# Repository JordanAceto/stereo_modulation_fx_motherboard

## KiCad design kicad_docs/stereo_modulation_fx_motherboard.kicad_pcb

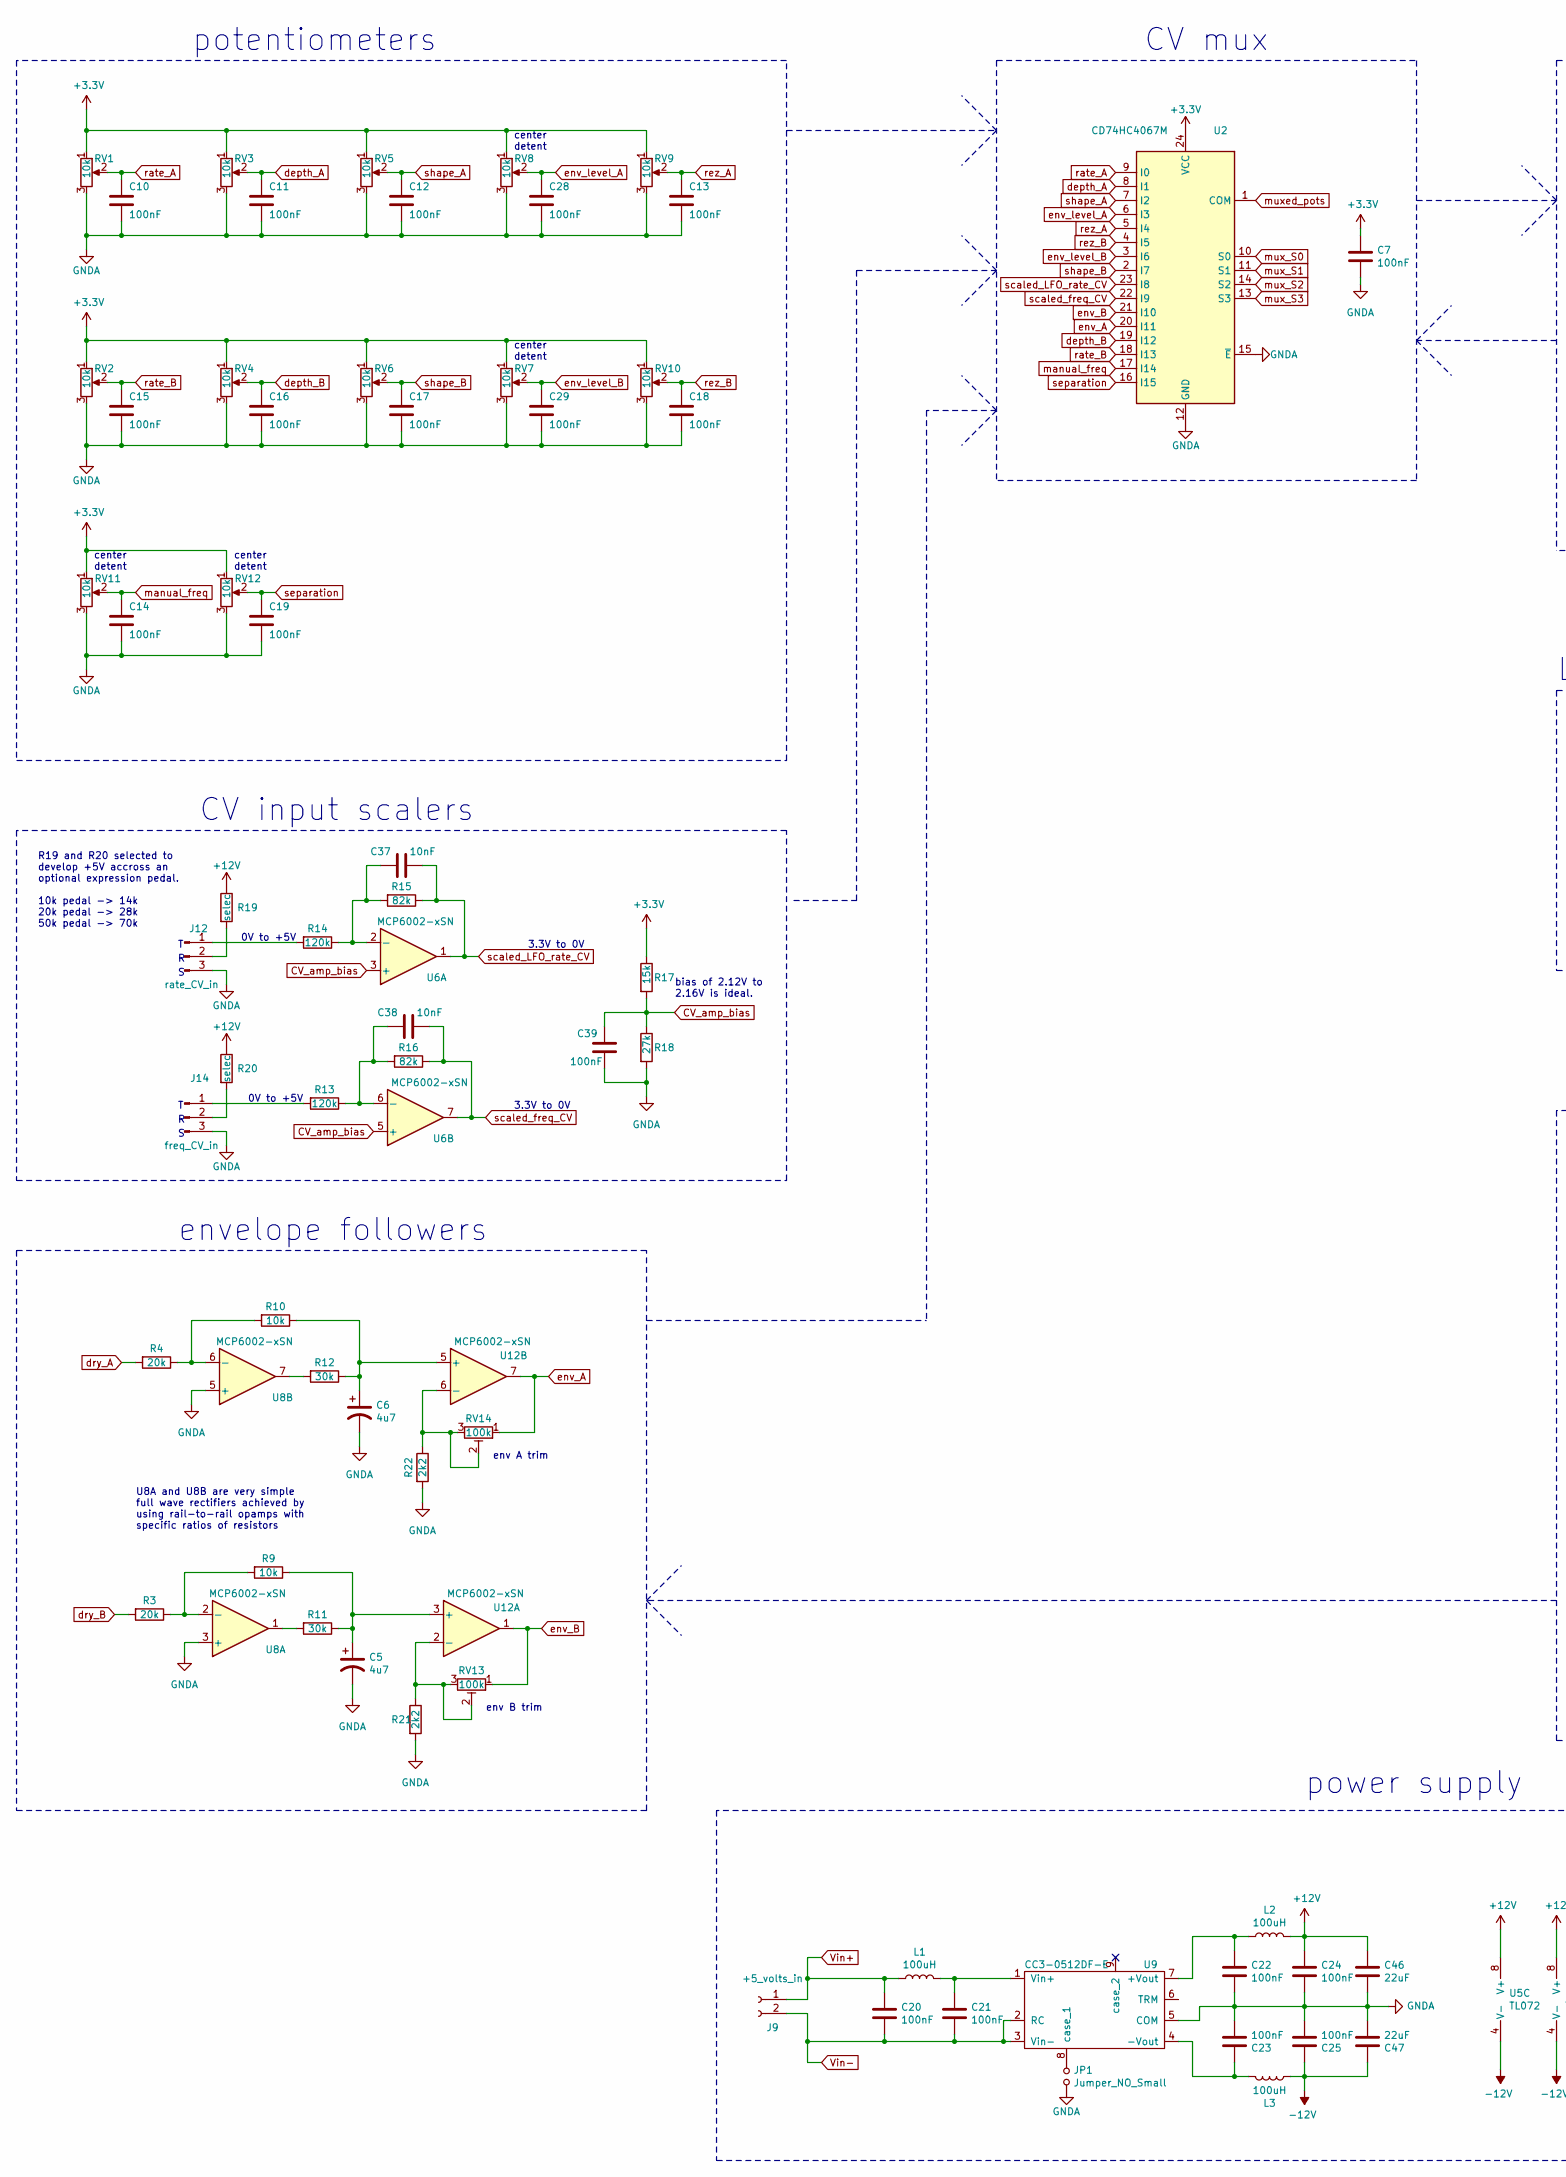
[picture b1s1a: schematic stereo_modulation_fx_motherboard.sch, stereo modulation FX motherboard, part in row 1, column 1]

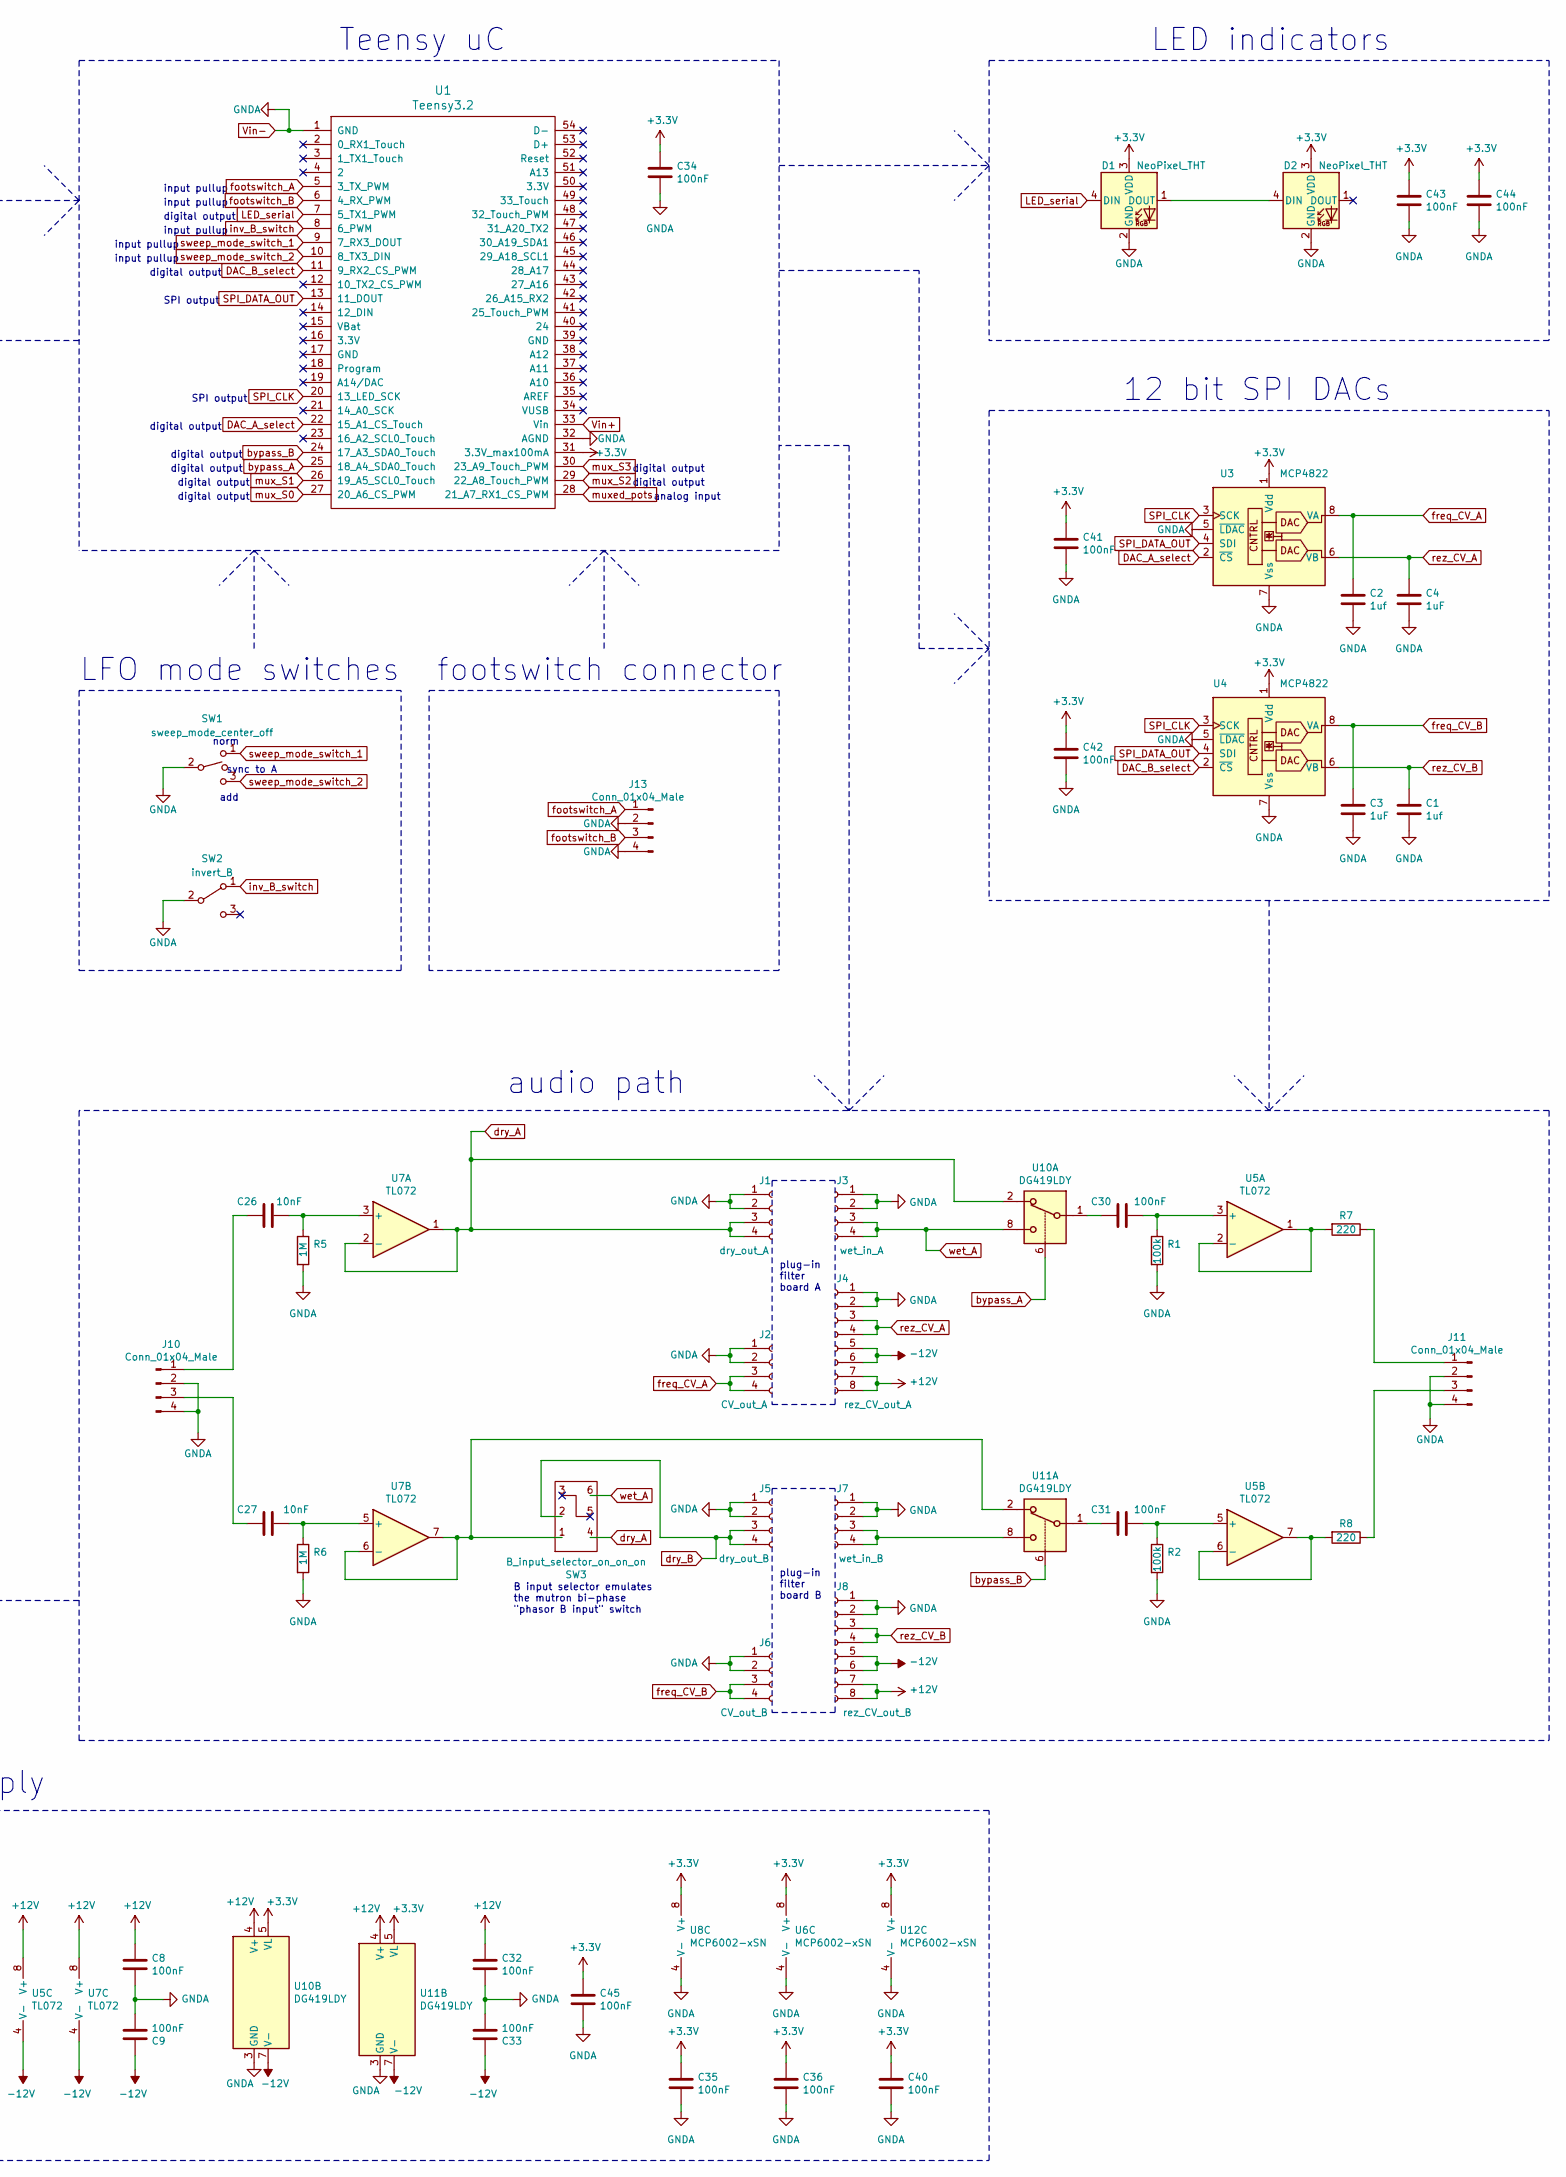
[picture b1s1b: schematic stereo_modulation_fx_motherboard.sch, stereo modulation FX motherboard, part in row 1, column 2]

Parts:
C1, C2: 1uf; C_0805_2012Metric_Pad1.15x1.40mm_HandSolder
C3, C4: 1uF; C_0805_2012Metric_Pad1.15x1.40mm_HandSolder
C5, C6: 4u7; C_0805_2012Metric_Pad1.15x1.40mm_HandSolder
C7, C8, C9, C10, C11, C12, C13, C14, C15, C16, C17, C18, C19, C20, C21, C22, C23, C24, C25, C28, C29, C30, C31, C32, C33, C34, C35, C36, C39, C40, C41, C42, C43, C44, C45: 100nF; C_0805_2012Metric_Pad1.15x1.40mm_HandSolder
C26, C27, C37, C38: 10nF; C_0805_2012Metric_Pad1.15x1.40mm_HandSolder
C46, C47: 22uF; C_0805_2012Metric_Pad1.15x1.40mm_HandSolder
D1, D2: NeoPixel_THT; LED_D5.0mm-4_RGB
J1: dry_out_A; PinSocket_1x04_P2.54mm_Vertical
J2: CV_out_A; PinSocket_1x04_P2.54mm_Vertical
J3: wet_in_A; PinSocket_1x04_P2.54mm_Vertical
J4: rez_CV_out_A; PinSocket_1x08_P2.54mm_Vertical
J5: dry_out_B; PinSocket_1x04_P2.54mm_Vertical
J6: CV_out_B; PinSocket_1x04_P2.54mm_Vertical
J7: wet_in_B; PinSocket_1x04_P2.54mm_Vertical
J8: rez_CV_out_B; PinSocket_1x08_P2.54mm_Vertical
J9: +5_volts_in; PinHeader_1x02_P2.54mm_Vertical
J10, J11, J13: Conn_01x04_Male; PinHeader_1x04_P2.54mm_Vertical
J12: rate_CV_in; PinHeader_1x03_P2.54mm_Vertical
J14: freq_CV_in; PinHeader_1x03_P2.54mm_Vertical
JP1: Jumper_NO_Small; SolderJumper-2_P1.3mm_Open_RoundedPad1.0x1.5mm
L1, L2, L3: 100uH; L_0805_2012Metric_Pad1.15x1.40mm_HandSolder
R1, R2: 100k; R_0805_2012Metric_Pad1.15x1.40mm_HandSolder
R3, R4: 20k; R_0805_2012Metric_Pad1.15x1.40mm_HandSolder
R5, R6: 1M; R_0805_2012Metric_Pad1.15x1.40mm_HandSolder
R7, R8: 220; R_0805_2012Metric_Pad1.15x1.40mm_HandSolder
R9, R10: 10k; R_0805_2012Metric_Pad1.15x1.40mm_HandSolder
R11, R12: 30k; R_0805_2012Metric_Pad1.15x1.40mm_HandSolder
R13, R14: 120k; R_0805_2012Metric_Pad1.15x1.40mm_HandSolder
R15, R16: 82k; R_0805_2012Metric_Pad1.15x1.40mm_HandSolder
R17: 15k; R_0805_2012Metric_Pad1.15x1.40mm_HandSolder
R18: 27k; R_0805_2012Metric_Pad1.15x1.40mm_HandSolder
R19, R20: selec; R_0805_2012Metric_Pad1.15x1.40mm_HandSolder
R21, R22: 2k2; R_0805_2012Metric_Pad1.15x1.40mm_HandSolder
RV1, RV2, RV3, RV4, RV5, RV6, RV7, RV8, RV9, RV10, RV11, RV12: 10k; Potentiometer_Alpha_RD901F-40-00D_Single_Vertical_CircularH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
RV13, RV14: 100k; Potentiometer_Bourns_3269W_Vertical
SW1: sweep_mode_center_off; SPDT_on_on
SW2: invert_B; SPDT_on_on
SW3: B_input_selector_on_on_on; DPDT_on_on_on
U1: Teensy3.2; teensy_3.2
U2: CD74HC4067M; SOIC-24W_7.5x15.4mm_P1.27mm
U3, U4: MCP4822; SOIC-8_3.9x4.9mm_P1.27mm
U5, U7: TL072; SOIC-8_3.9x4.9mm_P1.27mm
U6, U8, U12: MCP6002-xSN; SOIC-8_3.9x4.9mm_P1.27mm
U9: CC3-0512DF-E
U10, U11: DG419LDY; SOIC-8_3.9x4.9mm_P1.27mm

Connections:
+3V3: C7.1, C34.1, C35.1, C36.1, C40.1, C41.1, C42.1, C43.1, C44.1, C45.1, D1.3 (VDD), D2.3 (VDD), R17.1, RV1.1, RV2.1, RV3.1, RV4.1, RV5.1, RV6.1, RV7.1, RV8.1, RV9.1, RV10.1, RV11.1, RV12.1, U1.31 (3.3V_max100mA), U2.24 (VCC), U3.1 (Vdd), U4.1 (Vdd), U6.8 (V+), U8.8 (V+), U10.5 (VL), U11.5 (VL), U12.8 (V+)
+12V: C8.1, C24.1, C32.1, C46.1, J4.7, J4.8, J8.7, J8.8, L2.2, R19.1, R20.1, U5.8 (V+), U7.8 (V+), U10.4 (V+), U11.4 (V+)
-12V: C9.1, C25.1, C33.1, C47.1, J4.5, J4.6, J8.5, J8.6, L3.2, U5.4 (V-), U7.4 (V-), U10.7 (V-), U11.7 (V-)
CV_amp_bias: C39.1, R17.2, R18.1, U6.3 (+), U6.5 (+)
DAC_A_select: U1.22 (15_A1_CS_Touch), U3.2 (~CS)
DAC_B_select: U1.11 (9_RX2_CS_PWM), U4.2 (~CS)
LED_serial: D1.4 (DIN), U1.7 (5_TX1_PWM)
LFO_rate_CV_in: J12.1, R14.2
unnamed: C5.1, R9.1, R11.1, U12.3 (+)
unnamed: C6.1, R10.1, R12.1, U12.5 (+)
unnamed: C21.1, L1.2, U9.1 (Vin+)
unnamed: C22.1, L2.1, U9.7 (+Vout)
unnamed: C23.1, L3.1, U9.4 (-Vout)
unnamed: C26.1, R5.1, U7.3 (+)
unnamed: C26.2, J10.1
unnamed: C27.1, R6.1, U7.5 (+)
unnamed: C27.2, J10.3
unnamed: C30.1, R1.1, U5.3 (+)
unnamed: C30.2, U10.1
unnamed: C31.1, R2.1, U5.5 (+)
unnamed: C31.2, U11.1
unnamed: C37.2, R14.1, R15.2, U6.2 (-)
unnamed: C38.2, R13.1, R16.2, U6.6 (-)
unnamed: D1.1 (DOUT), D2.4 (DIN)
unnamed: J7.3, J7.4, U11.8
unnamed: J11.1, R7.1
unnamed: J11.3, R8.1
unnamed: J12.2, R19.2
unnamed: J14.2, R20.2
unnamed: JP1.1, U9.8 (case_1)
unnamed: R3.1, R9.2, U8.2 (-)
unnamed: R7.2, U5.1, U5.2 (-)
unnamed: R8.2, U5.6 (-), U5.7
unnamed: R4.1, R10.2, U8.6 (-)
unnamed: R11.2, U8.1
unnamed: R12.2, U8.7
unnamed: R21.1, RV13.2, RV13.3, U12.2 (-)
unnamed: R22.1, RV14.2, RV14.3, U12.6 (-)
unnamed: SW3.1, U7.6 (-), U7.7, U11.2
SPI_CLK: U1.20 (13_LED_SCK), U3.3 (SCK), U4.3 (SCK)
SPI_DATA_OUT: U1.13 (11_DOUT), U3.4 (SDI), U4.4 (SDI)
Vin+: C20.1, J9.1, L1.1, U1.33 (Vin)
Vin-: C1.2, C2.2, C3.2, C4.2, C5.2, C6.2, C7.2, C8.2, C9.2, C10.2, C11.2, C12.2, C13.2, C14.2, C15.2, C16.2, C17.2, C18.2, C19.2, C20.2, C21.2, C22.2, C23.2, C24.2, C25.2, C28.2, C29.2, C32.2, C33.2, C34.2, C35.2, C36.2, C39.2, C40.2, C41.2, C42.2, C43.2, C44.2, C45.2, C46.2, C47.2, D1.2 (GND), D2.2 (GND), J1.1, J1.2, J2.1, J2.2, J3.1, J3.2, J4.1, J4.2, J5.1, J5.2, J6.1, J6.2, J7.1, J7.2, J8.1, J8.2, J9.2, J10.2, J10.4, J11.2, J11.4, J12.3, J13.2, J13.4, J14.3, JP1.2, R1.2, R2.2, R5.2, R6.2, R18.2, R21.2, R22.2, RV1.3, RV2.3, RV3.3, RV4.3, RV5.3, RV6.3, RV7.3, RV8.3, RV9.3, RV10.3, RV11.3, RV12.3, SW1.2, SW2.2 (B), U1.1 (GND), U1.32 (AGND), U2.12 (GND), U2.15 (~E), U3.5 (~LDAC), U3.7 (Vss), U4.5 (~LDAC), U4.7 (Vss), U6.4 (V-), U8.3 (+), U8.4 (V-), U8.5 (+), U9.2 (RC), U9.3 (Vin-), U9.5 (COM), U10.3 (GND), U11.3 (GND), U12.4 (V-)
bypass_A: U1.25 (18_A4_SDA0_Touch), U10.6
bypass_B: U1.24 (17_A3_SDA0_Touch), U11.6
depth_A: C11.1, RV3.2, U2.8 (I1)
depth_B: C16.1, RV4.2, U2.19 (I12)
dry_A: J1.3, J1.4, R4.2, SW3.4, U7.1, U7.2 (-), U10.2
dry_B: J5.3, J5.4, R3.2, SW3.2
env_A: RV14.1, U2.20 (I11), U12.7
env_B: RV13.1, U2.21 (I10), U12.1
env_level_A: C28.1, RV8.2, U2.6 (I3)
env_level_B: C29.1, RV7.2, U2.3 (I6)
footswitch_A: J13.1, U1.5 (3_TX_PWM)
footswitch_B: J13.3, U1.6 (4_RX_PWM)
freq_CV_A: C2.1, J2.3, J2.4, U3.8 (VA)
freq_CV_B: C3.1, J6.3, J6.4, U4.8 (VA)
freq_CV_in: J14.1, R13.2
inv_B_switch: SW2.1 (A), U1.8 (6_PWM)
manual_freq: C14.1, RV11.2, U2.17 (I14)
mux_S0: U1.27 (20_A6_CS_PWM), U2.10 (S0)
mux_S1: U1.26 (19_A5_SCL0_Touch), U2.11 (S1)
mux_S2: U1.29 (22_A8_Touch_PWM), U2.14 (S2)
mux_S3: U1.30 (23_A9_Touch_PWM), U2.13 (S3)
muxed_pots: U1.28 (21_A7_RX1_CS_PWM), U2.1 (COM)
rate_A: C10.1, RV1.2, U2.9 (I0)
rate_B: C15.1, RV2.2, U2.18 (I13)
rez_A: C13.1, RV9.2, U2.5 (I4)
rez_B: C18.1, RV10.2, U2.4 (I5)
rez_CV_A: C4.1, J4.3, J4.4, U3.6 (VB)
rez_CV_B: C1.1, J8.3, J8.4, U4.6 (VB)
scaled_LFO_rate_CV: C37.1, R15.1, U2.23 (I8), U6.1
scaled_freq_CV: C38.1, R16.1, U2.22 (I9), U6.7
separation: C19.1, RV12.2, U2.16 (I15)
shape_A: C12.1, RV5.2, U2.7 (I2)
shape_B: C17.1, RV6.2, U2.2 (I7)
sweep_mode_switch_1: SW1.1, U1.9 (7_RX3_DOUT)
sweep_mode_switch_2: SW1.3, U1.10 (8_TX3_DIN)
wet_A: J3.3, J3.4, SW3.6, U10.8

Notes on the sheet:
norm
sync to A
add
0V to +5V
3.3V to 0V
envelope followers
CV input scalers
audio path
potentiometers
12 bit SPI DACs
LFO mode switches
CV mux
footswitch connector
input pullup
digital output
analog input
SPI output
LED indicators
bias of 2.12V to 2.16V is ideal.
Teensy uC
power supply
center detent
R19 and R20 selected to develop +5V accross an optional expression pedal. 10k pedal -> 14k 20k pedal -> 28k 50k pedal -> 70k
env A trim
env B trim
U8A and U8B are very simple full wave rectifiers achieved by using rail-to-rail opamps with specific ratios of resistors
B input selector emulates the mutron bi-phase "phasor B input" switch
plug-in filter board A
plug-in filter board B

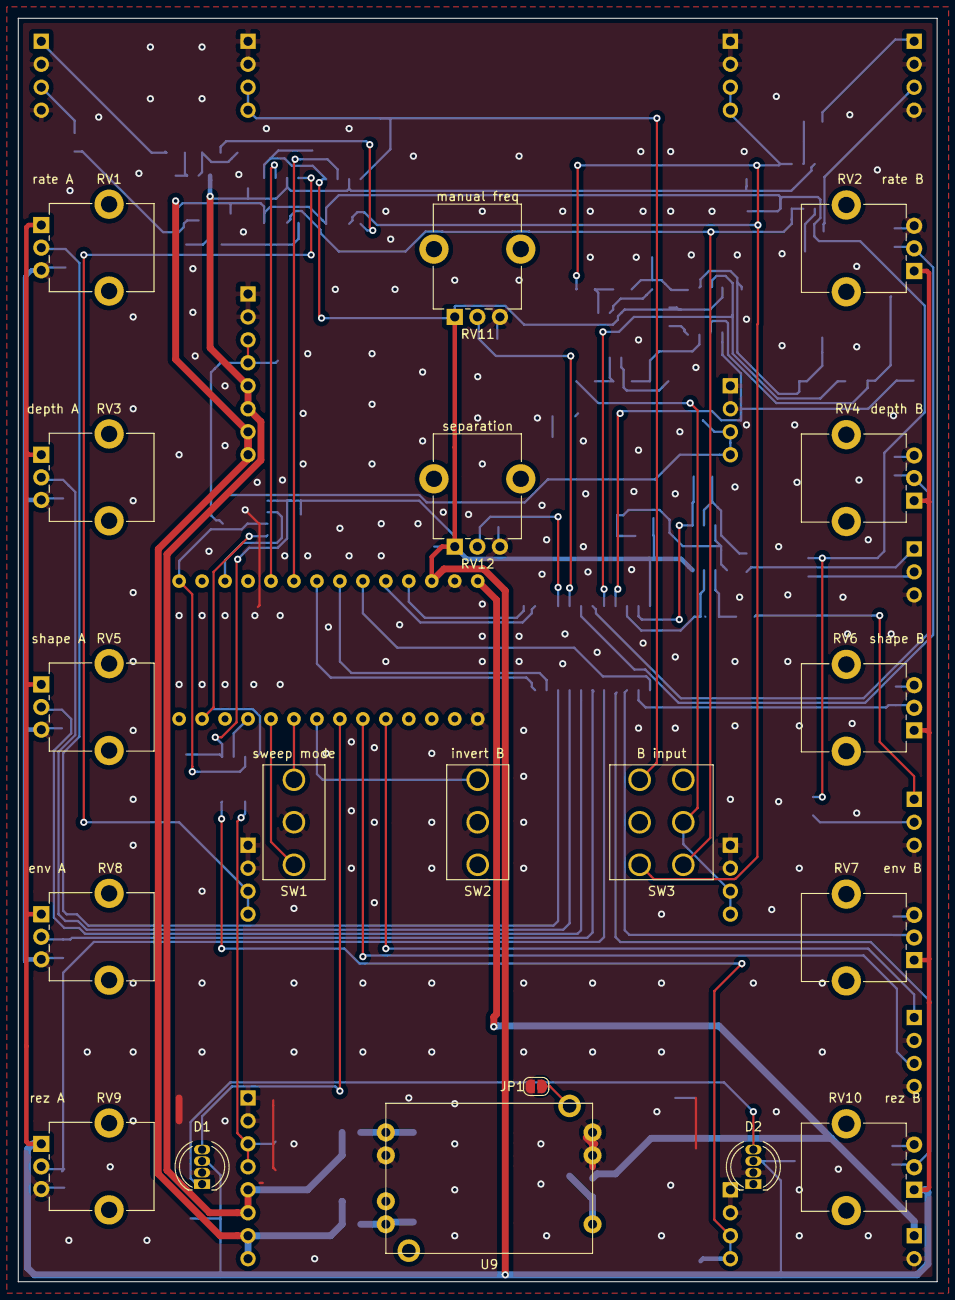
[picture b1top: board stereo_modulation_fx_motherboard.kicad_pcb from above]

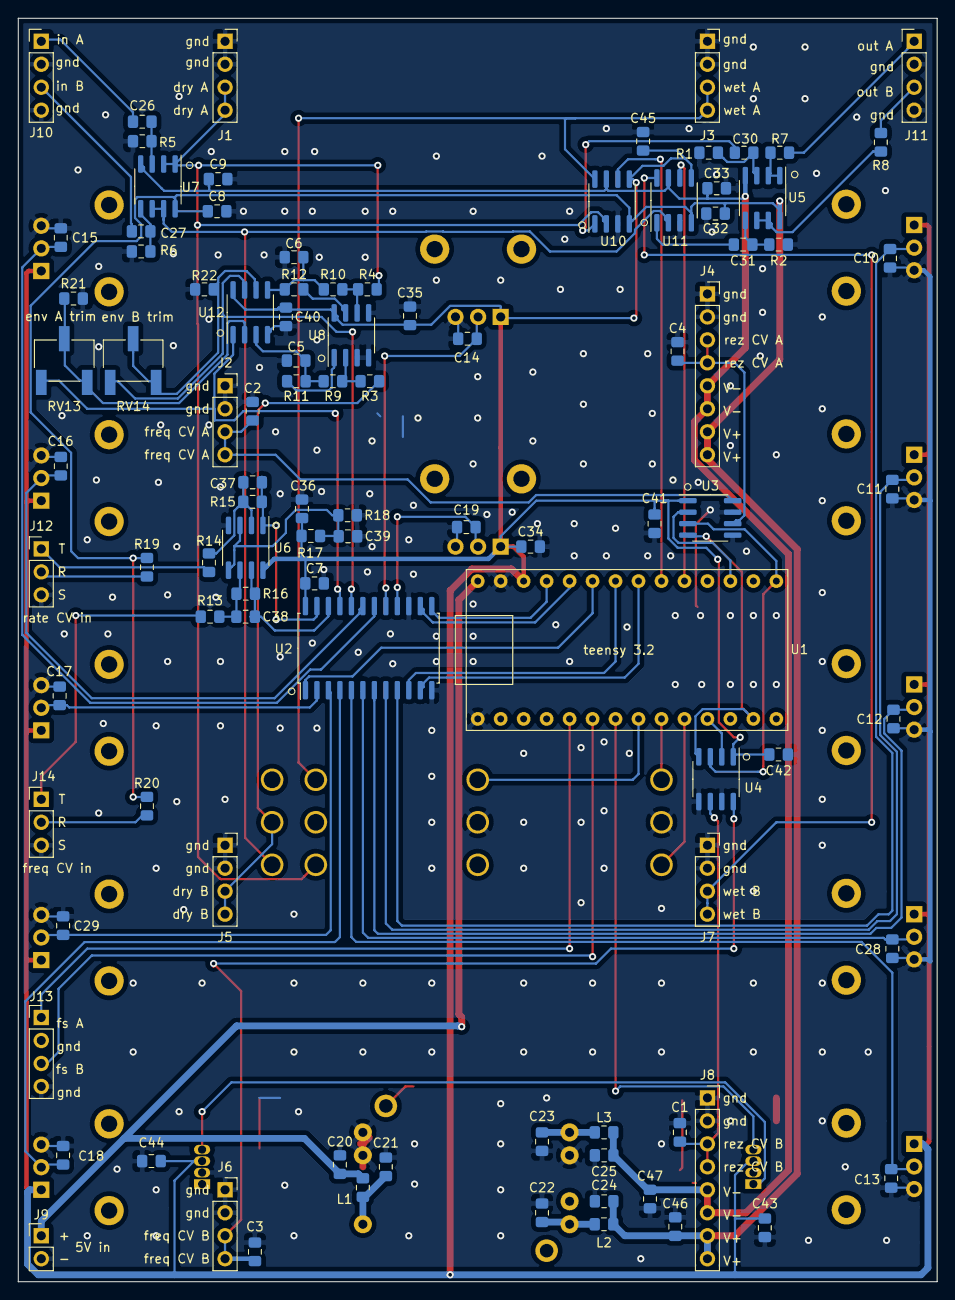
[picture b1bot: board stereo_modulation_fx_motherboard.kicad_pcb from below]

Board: 2 copper layers, 101.6 x 139.7 mm, 118 parts (99 on the bottom side), 79 nets.

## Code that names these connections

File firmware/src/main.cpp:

// just goofing around with some of the easy details

#include <Arduino.h>

#include <Bounce2.h>

Bounce bypass_switch_A = Bounce();
Bounce bypass_switch_B = Bounce();

const uint16_t DEBOUNCE_TIME = 25;

bool A_is_bypassed = false;
bool B_is_bypassed = false;

#include "LFO.h"

const double sample_rate = 3e3;

const uint32_t sample_period_in_microseconds = (1 / sample_rate) * 10e5;

uint32_t last_tick = 0;

LFO LFO_A(sample_rate);
LFO LFO_B(sample_rate);

#include "FastLED.h"

const int NUM_LEDS = 2;
CRGB led[NUM_LEDS];

enum LED
{
    A = 0,
    B = 1
};

#include "MCP4822.h"

const int CS_1_PIN = 15;
const int CS_2_PIN = 9;

MCP4822 dac_1(CS_1_PIN, MCP4822::Full_Scale_Output::TWO_POINT_ZERO_FOUR_EIGHT_VOLTS);
MCP4822 dac_2(CS_2_PIN, MCP4822::Full_Scale_Output::TWO_POINT_ZERO_FOUR_EIGHT_VOLTS);

#include "CD74HC4067.h"

const int MUX_S0 = 20;
const int MUX_S1 = 19;
const int MUX_S2 = 22;
const int MUX_S3 = 23;
const int MUX_COM = A7;

CD74HC4067 mux(MUX_S0, MUX_S1, MUX_S2, MUX_S3, MUX_COM);

enum CV_SOURCE
{
    // in order according to physical routing of the mux on the PCB
    // see schematic for details
    RATE_A = 0,
    DEPTH_A = 1,
    SHAPE_A = 2,
    ENV_LEVEL_A = 3,
    REZ_A = 4,
    RATE_B = 13,
    DEPTH_B = 12,
    SHAPE_B = 7,
    ENV_LEVEL_B = 6,
    REZ_B = 5,
    MANUAL_FREQ = 14,
    SEPARATION = 15,
    ENV_A = 11,
    ENV_B = 10,
    FREQ_CV = 9,
    RATE_CV = 8
};

enum SWEEP_MODE
{
    NORMAL,
    SYNC_TO_A,
    ADD
};

SWEEP_MODE sweep_mode = SWEEP_MODE::NORMAL;

bool B_is_inverted = false;

const int FOOTSWITCH_A_PIN = 3;
const int FOOTSWITCH_B_PIN = 4;

const int BYPASS_A_PIN = 18;
const int BYPASS_B_PIN = 17;

const int INVERT_B_SW_PIN = 6;
const int SWEEP_MODE_SW1_PIN = 7;
const int SWEEP_MODE_SW2_PIN = 8;

const int LED_SERIAL_PIN = 5;

const int FULL_SCALE = 0x0FFF; // for 12 bit DACs
const int HALF_SCALE = 0x07FF;

#include <array>

const int NUM_LFO_RATE_LUT_POINTS = 1 << 8;
const double APPROX_MAX_LFO_FREQ = 10.0;
const double APPROX_MIN_LFO_FREQ = 0.05;

// const lut generated by immediately-invoked lambda
const std::array<double, NUM_LFO_RATE_LUT_POINTS> LFO_rate_lut = []
{
    std::array<double, NUM_LFO_RATE_LUT_POINTS> arr;

    for (int i = 0; i < NUM_LFO_RATE_LUT_POINTS; i++)
    {
        double x = i;
        x = pow(x, 2);
        double squish_factor = pow(NUM_LFO_RATE_LUT_POINTS, 2) / APPROX_MAX_LFO_FREQ;
        x /= squish_factor;
        arr[i] = x + APPROX_MIN_LFO_FREQ; // small positive offset so rate is never zero
    }

    return arr;
}();

int32_t clampForDac(int32_t x);

void handleLFO_A_frequency();
void handleLFO_B_frequency();

int32_t getBipolarCVsource(CV_SOURCE source);
int32_t getUnipolarCVsource(CV_SOURCE source);

void setLEDtoRainbowFromCV(CRGB &led, int32_t CV);
void setLEDoff(CRGB &led);

void setup()
{

    analogReadResolution(12);

    bypass_switch_A.attach(BYPASS_A_PIN, INPUT_PULLUP);
    bypass_switch_B.attach(BYPASS_B_PIN, INPUT_PULLUP);
    bypass_switch_A.interval(DEBOUNCE_TIME);
    bypass_switch_B.interval(DEBOUNCE_TIME);

    pinMode(FOOTSWITCH_A_PIN, INPUT_PULLUP);
    pinMode(FOOTSWITCH_B_PIN, INPUT_PULLUP);

    pinMode(BYPASS_A_PIN, OUTPUT);
    pinMode(BYPASS_B_PIN, OUTPUT);

    pinMode(INVERT_B_SW_PIN, INPUT_PULLUP);

    pinMode(SWEEP_MODE_SW1_PIN, INPUT_PULLUP);
    pinMode(SWEEP_MODE_SW2_PIN, INPUT_PULLUP);

    pinMode(LED_SERIAL_PIN, OUTPUT);

    FastLED.addLeds<NEOPIXEL, LED_SERIAL_PIN>(led, NUM_LEDS);

    digitalWrite(BYPASS_A_PIN, HIGH);
    digitalWrite(BYPASS_B_PIN, HIGH);
}

void loop()
{
    if ((micros() - last_tick) > sample_period_in_microseconds)
    {
        last_tick = micros();

        bypass_switch_A.update();
        bypass_switch_B.update();

        if (bypass_switch_A.fell())
        {
            A_is_bypassed = !A_is_bypassed;
            digitalWrite(BYPASS_A_PIN, A_is_bypassed);
        }

        if (bypass_switch_B.fell())
        {
            B_is_bypassed = !B_is_bypassed;
            digitalWrite(BYPASS_B_PIN, B_is_bypassed);
        }

        if (digitalRead(SWEEP_MODE_SW1_PIN) && !digitalRead(SWEEP_MODE_SW2_PIN))
        {
            sweep_mode = SWEEP_MODE::NORMAL;
        }
        else if (digitalRead(SWEEP_MODE_SW1_PIN) && digitalRead(SWEEP_MODE_SW2_PIN))
        {
            sweep_mode = SWEEP_MODE::SYNC_TO_A;
        }
        else
        {
            sweep_mode = SWEEP_MODE::ADD;
        }

        B_is_inverted = !digitalRead(INVERT_B_SW_PIN);

        handleLFO_A_frequency();
        handleLFO_B_frequency();

        LFO_A.tick();
        LFO_B.tick();

        int32_t manual_freq = getBipolarCVsource(CV_SOURCE::MANUAL_FREQ);
        int32_t separation = getBipolarCVsource(CV_SOURCE::SEPARATION) >> 1;

        double lfo_A_scanner_position = (double)getUnipolarCVsource(CV_SOURCE::SHAPE_A) / FULL_SCALE;
        double lfo_B_scanner_position = (double)getUnipolarCVsource(CV_SOURCE::SHAPE_B) / FULL_SCALE;

        int32_t lfo_A = (LFO_A.getOutput(lfo_A_scanner_position) + 1.0) * ((2 << 10) - 1) - HALF_SCALE;
        int32_t depth_A = getUnipolarCVsource(CV_SOURCE::DEPTH_A);
        int32_t lfo_B = (LFO_B.getOutput(lfo_B_scanner_position) + 1.0) * ((2 << 10) - 1) - HALF_SCALE;
        int32_t depth_B = getUnipolarCVsource(CV_SOURCE::DEPTH_B);

        int32_t CV_A = 0;
        int32_t CV_B = 0;

        CV_A += manual_freq;
        CV_B += manual_freq;
        CV_A -= separation;
        CV_B += separation;

        if (sweep_mode == SWEEP_MODE::NORMAL)
        {
            // filter A gets LFO A
            CV_A += (lfo_A * depth_A) / FULL_SCALE;

            // filter B gets inverted or non-inverted LFO B
            if (B_is_inverted)
            {
                CV_B -= (lfo_B * depth_B) / FULL_SCALE;
            }
            else
            {
                CV_B += (lfo_B * depth_B) / FULL_SCALE;
            }
        }
        else if (sweep_mode == SWEEP_MODE::SYNC_TO_A)
        {
            // filter A gets LFO A
            CV_A += (lfo_A * depth_A) / FULL_SCALE;

            // filter B gets inverted or non-inverted LFO A
            if (B_is_inverted)
            {
                CV_B -= (lfo_A * depth_B) / FULL_SCALE;
            }
            else
            {
                CV_B += (lfo_A * depth_B) / FULL_SCALE;
            }
        }
        else if (sweep_mode == SWEEP_MODE::ADD)
        {
            int32_t lfo_A_contrib = (lfo_A * depth_A) / FULL_SCALE;
            int32_t lfo_B_contrib = (lfo_B * depth_B) / FULL_SCALE;

            // filter A gets LFO A plus LFO B
            CV_A += lfo_A_contrib;
            CV_A += lfo_B_contrib;

            // filter B gets LFO B plus inverted or non-inverted LFO A
            CV_B += lfo_B_contrib;

            if (B_is_inverted)
            {
                CV_B -= lfo_A_contrib;
            }
            else
            {
                CV_B += lfo_A_contrib;
            }
        }

        int32_t env_A = getBipolarCVsource(CV_SOURCE::ENV_A);
        env_A *= getBipolarCVsource(CV_SOURCE::ENV_LEVEL_A);
        env_A /= HALF_SCALE;
        CV_A -= env_A;

        int32_t env_B = getBipolarCVsource(CV_SOURCE::ENV_B);
        env_B *= getBipolarCVsource(CV_SOURCE::ENV_LEVEL_B);
        env_B /= HALF_SCALE;
        CV_B -= env_B;

        CV_A = clampForDac(CV_A + HALF_SCALE);
        CV_B = clampForDac(CV_B + HALF_SCALE);

        dac_1.setOutput(MCP4822::Channel::A, CV_A);
        dac_1.setOutput(MCP4822::Channel::B, getUnipolarCVsource(CV_SOURCE::REZ_A));

        dac_2.setOutput(MCP4822::Channel::A, CV_B);
        dac_2.setOutput(MCP4822::Channel::B, getUnipolarCVsource(CV_SOURCE::REZ_B));

        if (A_is_bypassed)
        {
            setLEDoff(led[LED::A]);
        }
        else
        {
            setLEDtoRainbowFromCV(led[LED::A], CV_A);
        }

        if (B_is_bypassed)
        {
            setLEDoff(led[LED::B]);
        }
        else
        {
            setLEDtoRainbowFromCV(led[LED::B], CV_B);
        }
    }

    EVERY_N_MILLISECONDS(20)
    {
        FastLED.show();
    }
}

int32_t clampForDac(int32_t x)
{
    if (x < 0)
    {
        return 0;
    }
    else if (x > FULL_SCALE)
    {
        return FULL_SCALE;
    }
    else
    {
        return x;
    }
}

int32_t getBipolarCVsource(CV_SOURCE source)
{
    mux.select(source);
    int32_t CV = (FULL_SCALE - mux.analogReadCom());
    CV -= HALF_SCALE;
    return CV;
}

int32_t getUnipolarCVsource(CV_SOURCE source)
{
    mux.select(source);
    return FULL_SCALE - mux.analogReadCom();
}

void setLEDtoRainbowFromCV(CRGB &led, int32_t CV)
{
    led = CHSV(((CV / 18) + 130) % 256 , 225, 50);
}

void setLEDoff(CRGB &led)
{
    led = CRGB::Black;
}

void handleLFO_A_frequency()
{
    double rate_a = LFO_rate_lut[getUnipolarCVsource(CV_SOURCE::RATE_A) >> 4];
    LFO_A.setFrequency(rate_a);
}

void handleLFO_B_frequency()
{
    double rate_b = LFO_rate_lut[getUnipolarCVsource(CV_SOURCE::RATE_B) >> 4];
    LFO_B.setFrequency(rate_b);
}

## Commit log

2019-05-23 initial commit, NOT DONE! DO NOT ORDER BOARDS!
2019-05-24 add note about wet/dry mix polarity to schem, will need to be addressed
2019-05-25 add wet/dry mix inverter, tidy up board, NOT DONE DO NOT ORDER BOARDS!
2019-05-25 add input buffers, misc tidy up, NOT DONE DO NOT ORDER BOARDS!
2019-05-26 change DACs to MCP4822, misc tidy up, DO NOT ORDER BOARDS!
2019-05-27 remove wet/dry mixer, replace with envelope follower, NOT DONE DO NOT ORDER BOARDS!
2019-05-28 continue working on layout, NOT DONE!
2019-05-30 move all components to one side of board, play with trace layout, NOT DONEgit add -A!
2019-05-31 move traces/vias away from pot tabs, progress on routing, NOT DONEgit add -A!
2019-05-31 move schematic blocks around, add LEDs
2019-06-05 plug in boards are smaller now
2019-06-06 tidy schematic, add stitching vias
2019-06-07 restrucure files, begin firmware
2019-06-07 begin BOM, add pdf of schematic
2019-06-07 fill in BOM
2019-06-07 restructure firmware dir
2019-06-07 refine BOM
2019-06-07 tidy up BOM
2019-06-10 correct BOM mistake, more BOM errors probably lurk
2019-06-10 work on BOM, inductors are still wrong
2019-06-15 add parts list to construction docs
2019-06-15 add problems with rev 1 txt file
2019-06-15 mess around with firmware after getting rev 1 board
2019-06-15 minor changes to pcb
2019-06-15 restructure firmware, move DAC and MUX files to lib folder
2019-06-15 add phase accumulator to firmware
2019-06-15 work on waveshapers for LFO
2019-06-15 add beginning of LFO class, no scanner yet
2019-06-21 add to list of probs with rev 1 board
2019-06-21 add crosshair drill marks to pcb user drawings
2019-06-21 play around with firmware
2019-07-15 get basic firmware working except LFO wave scanners
2019-07-16 add Trapezoid_Generator and Scanner classes, used for LFO wave scanning
2019-07-16 make LFO class work with wave scanner
2019-07-16 apply lfo wave scanning to main
2019-07-16 fix random wave shaper

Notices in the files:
kicad_docs/stereo_modulation_fx_motherboard.kicad_pcb:
License: CC by 4.0
kicad_docs/stereo_modulation_fx_motherboard.sch:
creativecommons.org/licenses/by/4.0
